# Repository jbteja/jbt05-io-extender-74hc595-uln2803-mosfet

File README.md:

# IO extender for switching low-current motors and solenoid valves
> Image of the board:

> 3D view of the board:
<figure class="video_container">
  <video controls="true" allowfullscreen="true">
    <source src="3D/rev-0.1.1.mp4" type="video/mp4">
  </video>
</figure>

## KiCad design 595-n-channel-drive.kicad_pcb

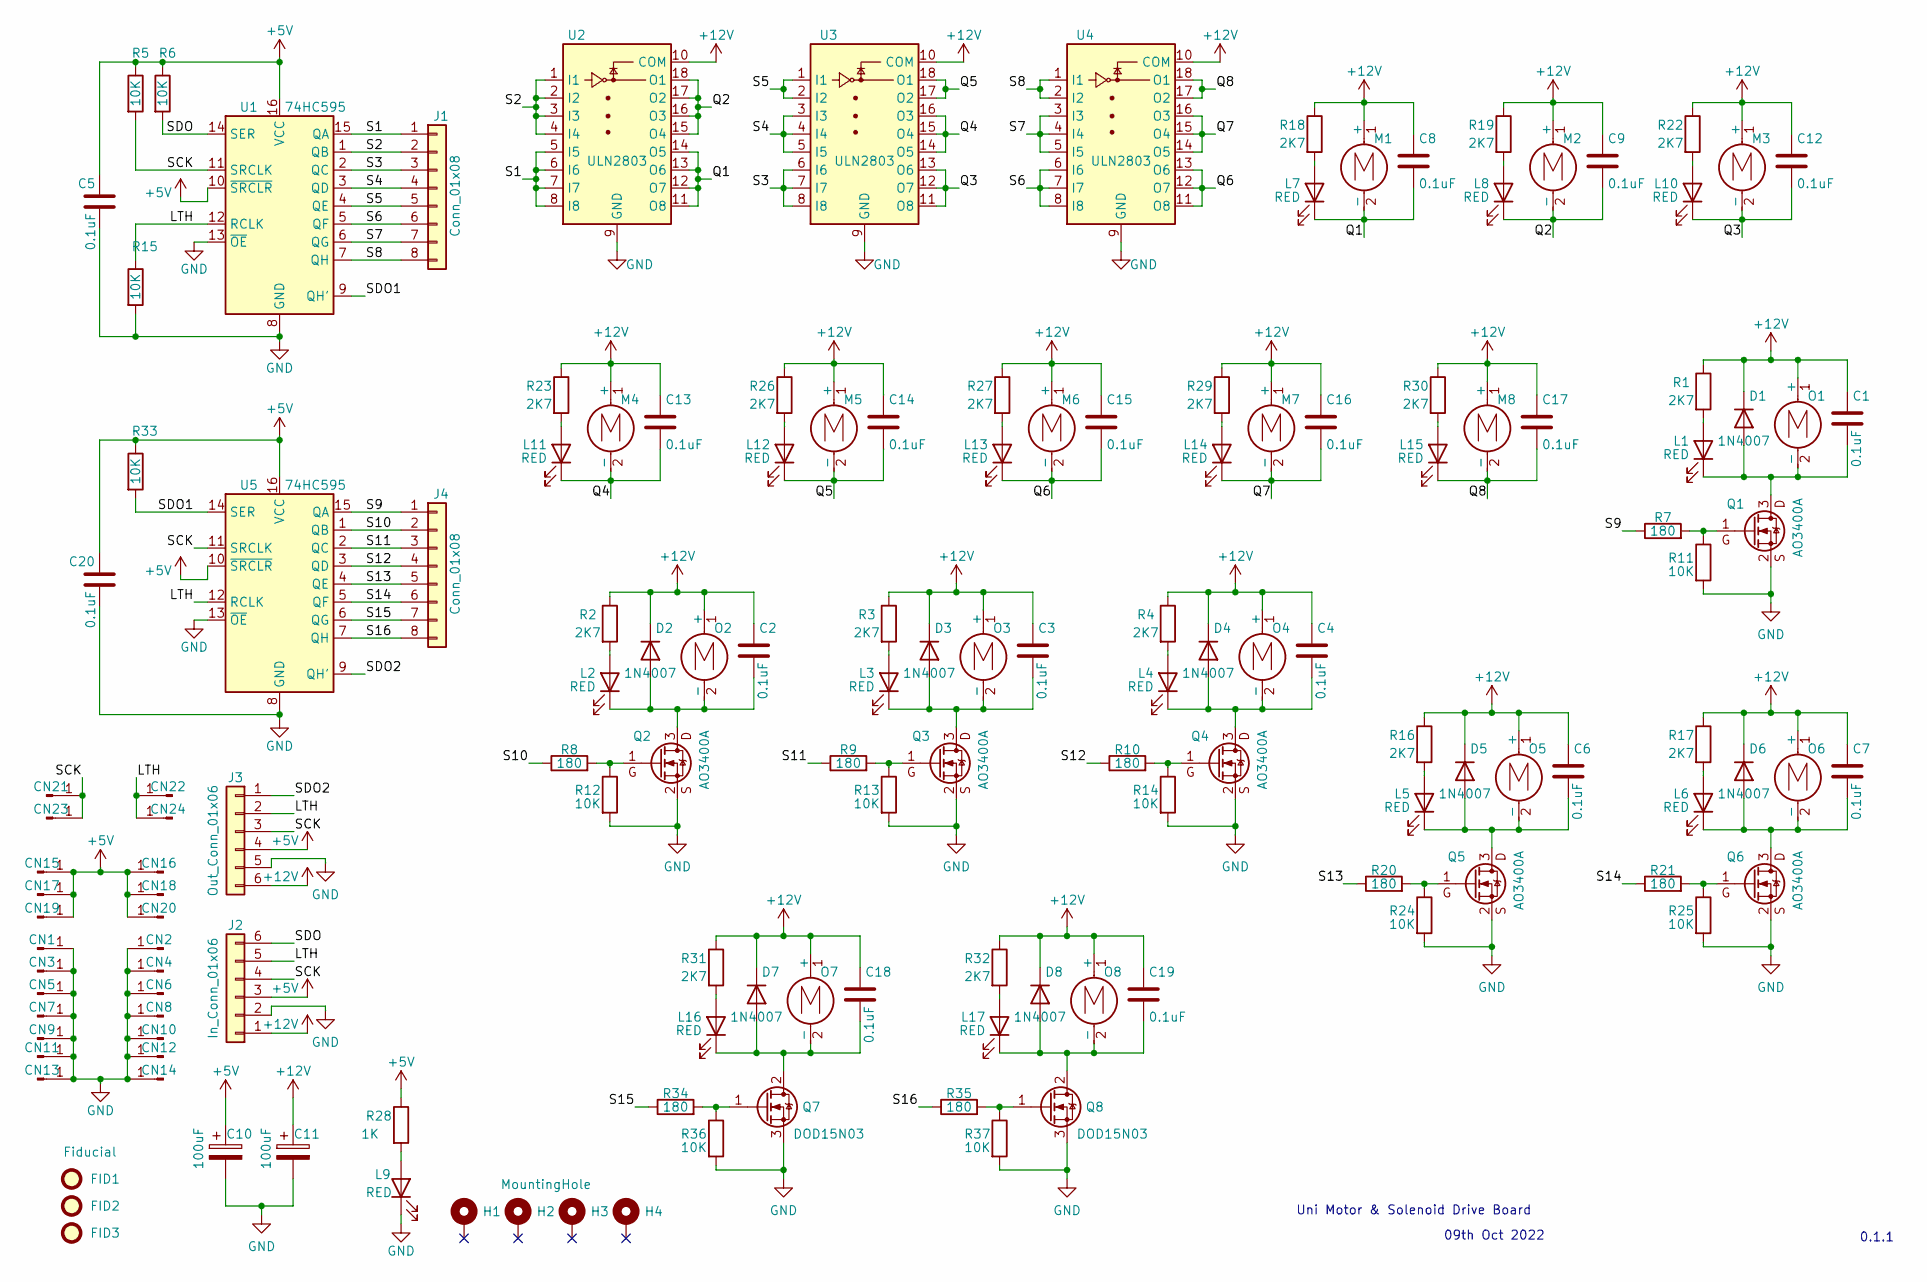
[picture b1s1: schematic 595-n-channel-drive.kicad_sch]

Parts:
C1, C2, C3, C4, C5, C6, C7, C8, C9, C12, C13, C14, C15, C16, C17, C18, C19, C20: 0.1uF; C_0805_2012Metric
C10: 100uF; CP_Elec_6.3x7.7
C11: 100uF; CP_Elec_10x10
CN1, CN2, CN3, CN4, CN5, CN6, CN7, CN8, CN9, CN10, CN11, CN12, CN13, CN14, CN15, CN16, CN17, CN18, CN19, CN20, CN21, CN22, CN23, CN24: Conn_01x01_Male; 1X01
D1, D2, D3, D4, D5, D6, D7, D8: 1N4007; D_SMA
FID1, FID2, FID3: Fiducial; Fiducial_0.5mm_Mask1mm
H1, H2, H3, H4: MountingHole; MountingHole_3.2mm_M3_Pad
J1, J4: Conn_01x08; PinHeader_1x08_P2.54mm_Vertical
J2: In_Conn_01x06; JST_EH_S6B-EH_1x06_P2.50mm_Horizontal
J3: Out_Conn_01x06; JST_EH_S6B-EH_1x06_P2.50mm_Horizontal
L1, L2, L3, L4, L5, L6, L7, L8, L9, L10, L11, L12, L13, L14, L15, L16, L17: RED; LED_0805_2012Metric
M1, M2, M3, M4, M5, M6, M7, M8: Motor_DC; JST_EH_S2B-EH_1x02_P2.50mm_Horizontal
O1, O2, O3, O4, O5, O6, O7, O8: Motor_DC; JST_EH_S2B-EH_1x02_P2.50mm_Horizontal
Q1, Q2, Q3, Q4, Q5, Q6: AO3400A; SOT-23
Q7, Q8: DOD15N03; TO-252-2
R1, R2, R3, R4, R16, R17, R18, R19, R22, R23, R26, R27, R29, R30, R31, R32: 2K7; R_0805_2012Metric
R5, R6, R11, R12, R13, R14, R15, R24, R25, R33, R36, R37: 10K; R_0805_2012Metric
R7, R8, R9, R10, R20, R21, R34, R35: 180; R_0805_2012Metric
R28: 1K; R_0805_2012Metric
U1, U5: 74HC595; SOIC-16_3.9x9.9mm_P1.27mm
U2, U3, U4: ULN2803; SOIC-18W_7.5x11.6mm_P1.27mm

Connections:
+5V: C5.1, C10.1, C20.1, CN15.1, CN16.1, CN17.1, CN18.1, CN19.1, CN20.1, J2.3, J3.4, R5.1, R6.1, R28.1, R33.1, U1.10 (~SRCLR), U1.16 (VCC), U5.10 (~SRCLR), U5.16 (VCC)
+12V: C1.1, C2.1, C3.1, C4.1, C6.1, C7.1, C8.1, C9.1, C11.1, C12.1, C13.1, C14.1, C15.1, C16.1, C17.1, C18.1, C19.1, D1.1 (K), D2.1 (K), D3.1 (K), D4.1 (K), D5.1 (K), D6.1 (K), D7.1 (K), D8.1 (K), J2.1, J3.6, M1.1 (+), M2.1 (+), M3.1 (+), M4.1 (+), M5.1 (+), M6.1 (+), M7.1 (+), M8.1 (+), O1.1 (+), O2.1 (+), O3.1 (+), O4.1 (+), O5.1 (+), O6.1 (+), O7.1 (+), O8.1 (+), R1.1, R2.1, R3.1, R4.1, R16.1, R17.1, R18.1, R19.1, R22.1, R23.1, R26.1, R27.1, R29.1, R30.1, R31.1, R32.1, U2.10 (COM), U3.10 (COM), U4.10 (COM)
/LTH: CN22.1, CN24.1, J2.5, J3.2, R15.1, U1.12 (RCLK), U5.12 (RCLK)
/Q1: C8.2, L7.1 (K), M1.2 (-), U2.11 (O8), U2.12 (O7), U2.13 (O6), U2.14 (O5)
/Q2: C9.2, L8.1 (K), M2.2 (-), U2.15 (O4), U2.16 (O3), U2.17 (O2), U2.18 (O1)
/Q3: C12.2, L10.1 (K), M3.2 (-), U3.11 (O8), U3.12 (O7), U3.13 (O6)
/Q4: C13.2, L11.1 (K), M4.2 (-), U3.14 (O5), U3.15 (O4), U3.16 (O3)
/Q5: C14.2, L12.1 (K), M5.2 (-), U3.17 (O2), U3.18 (O1)
/Q6: C15.2, L13.1 (K), M6.2 (-), U4.11 (O8), U4.12 (O7), U4.13 (O6)
/Q7: C16.2, L14.1 (K), M7.2 (-), U4.14 (O5), U4.15 (O4), U4.16 (O3)
/Q8: C17.2, L15.1 (K), M8.2 (-), U4.17 (O2), U4.18 (O1)
/S1: J1.1, U1.15 (QA), U2.5 (I5), U2.6 (I6), U2.7 (I7), U2.8 (I8)
/S2: J1.2, U1.1 (QB), U2.1 (I1), U2.2 (I2), U2.3 (I3), U2.4 (I4)
/S3: J1.3, U1.2 (QC), U3.6 (I6), U3.7 (I7), U3.8 (I8)
/S4: J1.4, U1.3 (QD), U3.3 (I3), U3.4 (I4), U3.5 (I5)
/S5: J1.5, U1.4 (QE), U3.1 (I1), U3.2 (I2)
/S6: J1.6, U1.5 (QF), U4.6 (I6), U4.7 (I7), U4.8 (I8)
/S7: J1.7, U1.6 (QG), U4.3 (I3), U4.4 (I4), U4.5 (I5)
/S8: J1.8, U1.7 (QH), U4.1 (I1), U4.2 (I2)
/S9: J4.1, R7.1, U5.15 (QA)
/S10: J4.2, R8.1, U5.1 (QB)
/S11: J4.3, R9.1, U5.2 (QC)
/S12: J4.4, R10.1, U5.3 (QD)
/S13: J4.5, R20.1, U5.4 (QE)
/S14: J4.6, R21.1, U5.5 (QF)
/S15: J4.7, R34.1, U5.6 (QG)
/S16: J4.8, R35.1, U5.7 (QH)
/SCK: CN21.1, CN23.1, J2.4, J3.3, R5.2, U1.11 (SRCLK), U5.11 (SRCLK)
/SDO: J2.6, R6.2, U1.14 (SER)
/SDO1: R33.2, U1.9 (QH'), U5.14 (SER)
/SDO2: J3.1, U5.9 (QH')
GND: C5.2, C10.2, C11.2, C20.2, CN1.1, CN2.1, CN3.1, CN4.1, CN5.1, CN6.1, CN7.1, CN8.1, CN9.1, CN10.1, CN11.1, CN12.1, CN13.1, CN14.1, J2.2, J3.5, L9.1 (K), Q1.2 (S), Q2.2 (S), Q3.2 (S), Q4.2 (S), Q5.2 (S), Q6.2 (S), Q7.3 (S), Q8.3 (S), R11.2, R12.2, R13.2, R14.2, R15.2, R24.2, R25.2, R36.2, R37.2, U1.8 (GND), U1.13 (~OE), U2.9 (GND), U3.9 (GND), U4.9 (GND), U5.8 (GND), U5.13 (~OE)
unnamed: C1.2, D1.2 (A), L1.1 (K), O1.2 (-), Q1.3 (D)
unnamed: C2.2, D2.2 (A), L2.1 (K), O2.2 (-), Q2.3 (D)
unnamed: C3.2, D3.2 (A), L3.1 (K), O3.2 (-), Q3.3 (D)
unnamed: C4.2, D4.2 (A), L4.1 (K), O4.2 (-), Q4.3 (D)
unnamed: C6.2, D5.2 (A), L5.1 (K), O5.2 (-), Q5.3 (D)
unnamed: C7.2, D6.2 (A), L6.1 (K), O6.2 (-), Q6.3 (D)
unnamed: C18.2, D7.2 (A), L16.1 (K), O7.2 (-), Q7.2 (D)
unnamed: C19.2, D8.2 (A), L17.1 (K), O8.2 (-), Q8.2 (D)
unnamed: L1.2 (A), R1.2
unnamed: L2.2 (A), R2.2
unnamed: L3.2 (A), R3.2
unnamed: L4.2 (A), R4.2
unnamed: L5.2 (A), R16.2
unnamed: L6.2 (A), R17.2
unnamed: L7.2 (A), R18.2
unnamed: L8.2 (A), R19.2
unnamed: L9.2 (A), R28.2
unnamed: L10.2 (A), R22.2
unnamed: L11.2 (A), R23.2
unnamed: L12.2 (A), R26.2
unnamed: L13.2 (A), R27.2
unnamed: L14.2 (A), R29.2
unnamed: L15.2 (A), R30.2
unnamed: L16.2 (A), R31.2
unnamed: L17.2 (A), R32.2
unnamed: Q1.1 (G), R7.2, R11.1
unnamed: Q2.1 (G), R8.2, R12.1
unnamed: Q3.1 (G), R9.2, R13.1
unnamed: Q4.1 (G), R10.2, R14.1
unnamed: Q5.1 (G), R20.2, R24.1
unnamed: Q6.1 (G), R21.2, R25.1
unnamed: Q7.1 (G), R34.2, R36.1
unnamed: Q8.1 (G), R35.2, R37.1

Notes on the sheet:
0.1.1
09th Oct 2022
Uni Motor & Solenoid Drive Board

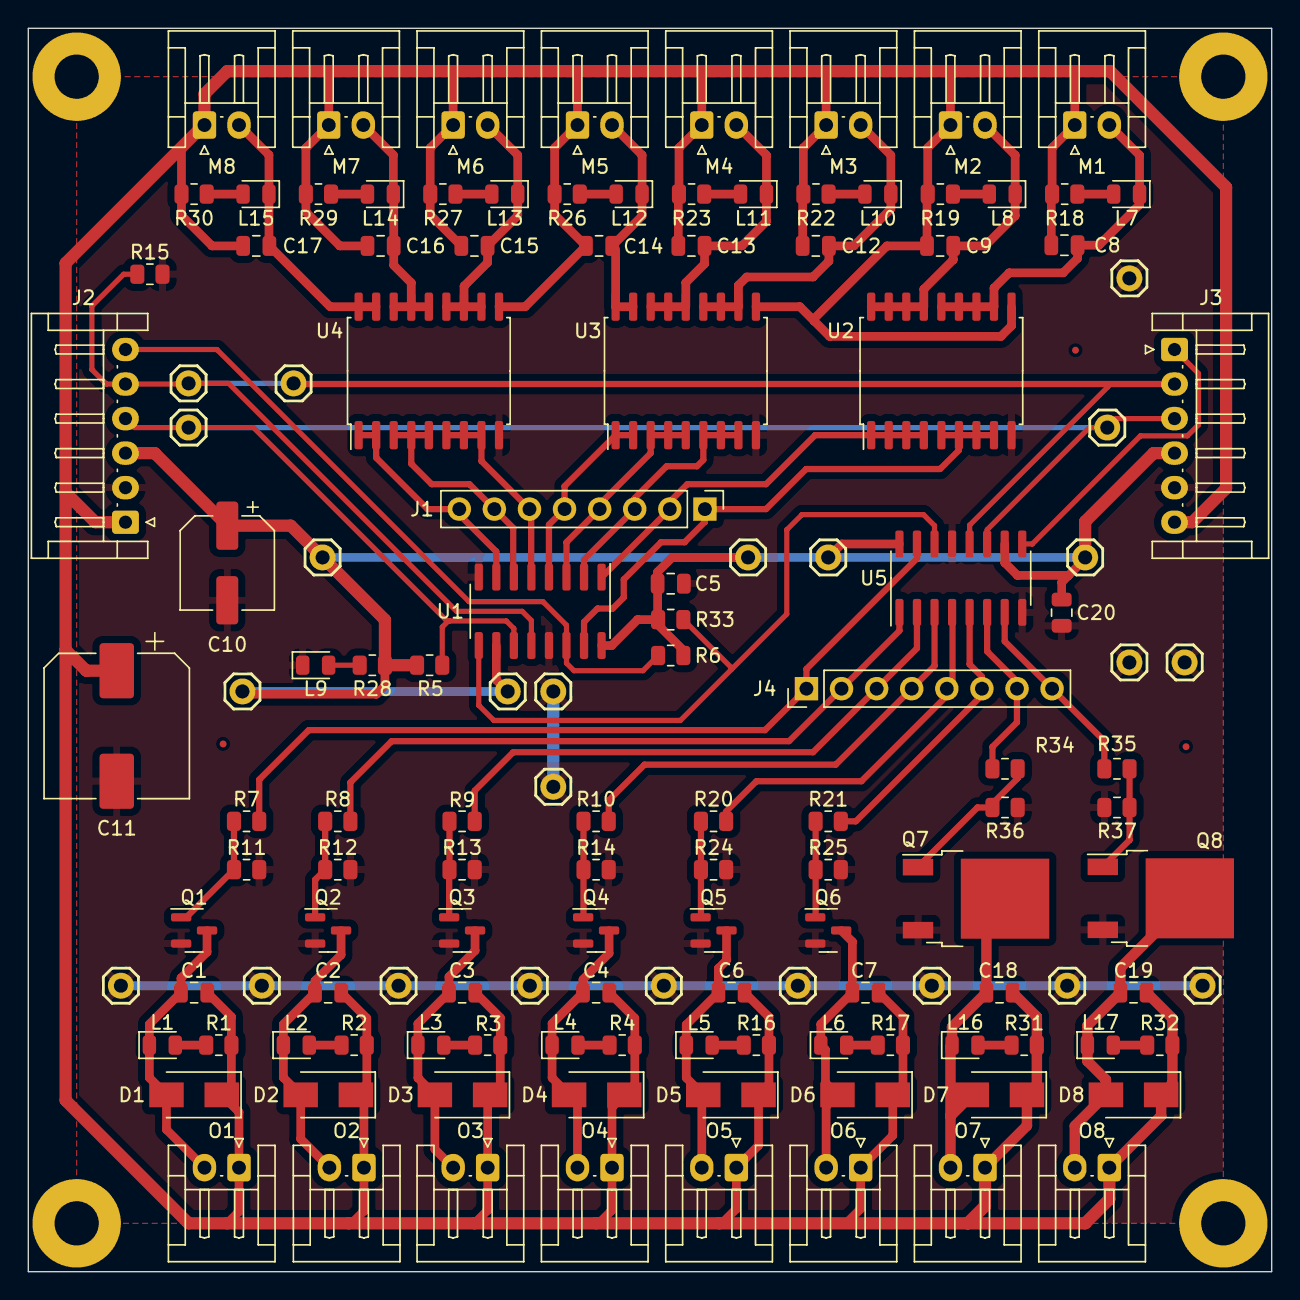
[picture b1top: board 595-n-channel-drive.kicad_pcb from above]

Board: 2 copper layers, 90.0 x 90.0 mm, 146 parts (0 on the bottom side), 65 nets.

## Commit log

2023-06-15 Initial commit, Pushing all the staged changes
2023-06-21 Adding 3D view of the board
2023-06-21 Updating 3D view, Typo
2023-06-21 Typo, Correction
